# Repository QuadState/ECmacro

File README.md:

# ECmacro

ECmacro is a series of small USB keyboards (macro pads) that use electrostatic capacitive switch parts.
No special external components are needed to read the keys: just the microcontroller's GPIO pins and one resistor per key.

## Models

| | ECmacro 2V | ECmacro 4H |
|---|---|---|
| Features | Volume control; press both keys to mute | Key assignments adjustable in Remap and VIA |
| Microcontroller | CH552E | Seeed Studio XIAO RP2040 |
| Firmware | Custom ([firmware/ch552](firmware/ch552/)) | QMK ([firmware/rp2040](firmware/rp2040/qmk/keyboards/quadstate/ecmacro4h/)) |
| Schematic and PCB | [hardware/2V](hardware/2V/) | [hardware/4H](hardware/4H/) |

## Contents

| Folder | Contents |
|---|---|
| [hardware/](hardware/) | Schematic and PCB for each model (KiCad 10) |
| [firmware/ch552/](firmware/ch552/) | Firmware for the CH552E models; its README covers building and flashing |
| [firmware/rp2040/](firmware/rp2040/) | QMK keyboard definition, VIA definition, build scripts, a udev rule for Linux, and the firmware's [license, source and third-party notices](firmware/rp2040/THIRD-PARTY-NOTICES.txt) |

Case design files are not included.

## USB ID

All models use the USB VID:PID `1209:EC02` ([pid.codes](https://pid.codes/1209/EC02/)).

## License

- Schematics and PCBs (hardware/), images (images/) and documentation outside firmware/rp2040/: CC BY 4.0
- CH552 firmware (firmware/ch552/): MIT
- RP2040 firmware (firmware/rp2040/, including its readme): GPL-2.0-or-later (distributed firmware: GPLv3)

See [LICENSE](LICENSE) for details and [LICENSES/](LICENSES/) for the full texts. For the firmware written on the ECmacro 4H, [firmware/rp2040/THIRD-PARTY-NOTICES.txt](firmware/rp2040/THIRD-PARTY-NOTICES.txt) gives its license, where to get its complete source code, how to build and install it, and its third-party notices.

Copyright (c) 2025–2026 QuadState

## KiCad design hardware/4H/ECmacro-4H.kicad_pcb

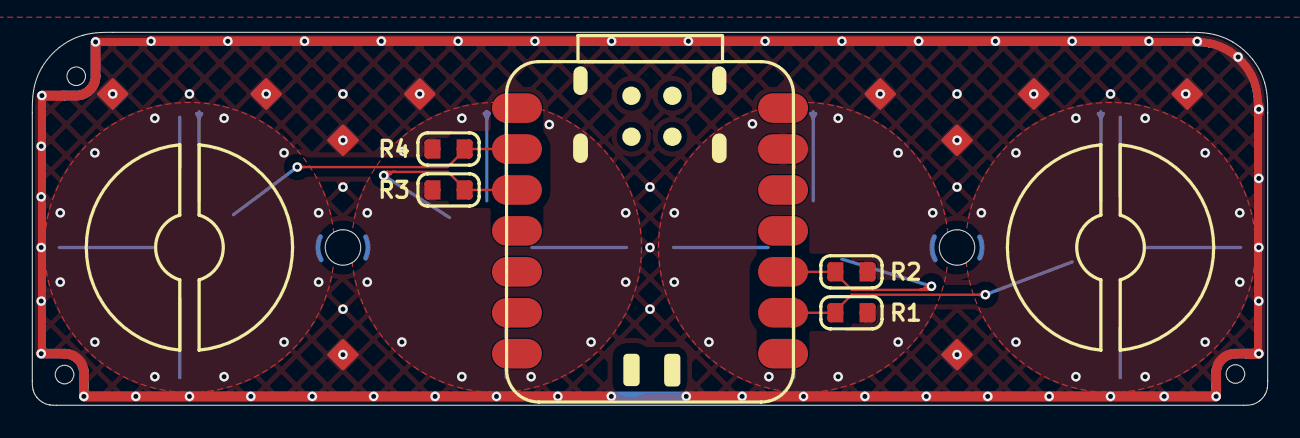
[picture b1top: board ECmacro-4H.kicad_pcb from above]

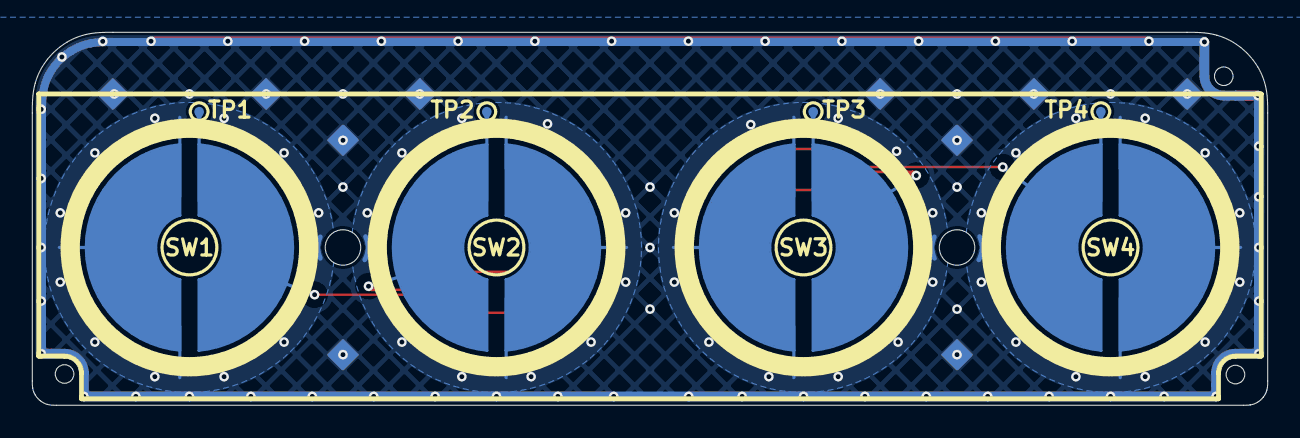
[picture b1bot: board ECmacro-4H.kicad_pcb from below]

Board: 2 copper layers, 76.7 x 23.1 mm, 18 parts (8 on the bottom side), 5 nets.

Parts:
R1, R2, R3, R4: 680kΩ; R_SMD_2012
SW1, SW2, SW3, SW4: SW_Cap; CapacitiveSwitch_16mm
TH1, TH2, TH3: ToolingHole_1.152mm
TH4, TH5: MountingHole_2.2mm_M2
TP1, TP2, TP3, TP4: TestPoint; TestPoint_Pad_D0.6mm
U2: XIAO RP2040; Module_XIAO_RP2040

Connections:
/SW1: R1.1, SW1.2, TP1.1 (1_1), U2.9 (D8)
/SW2: R2.1, SW2.1, TP2.1 (1_1), U2.10 (D9)
/SW3: R3.1, SW3.1, TP3.1 (1_1), U2.3 (D2)
/SW4: R4.1, SW4.1, TP4.1 (1_1), U2.2 (D1)
GND: R1.2, R2.2, R3.2, R4.2, SW1.1, SW2.2, SW3.2, SW4.2, U2.13 (GND)

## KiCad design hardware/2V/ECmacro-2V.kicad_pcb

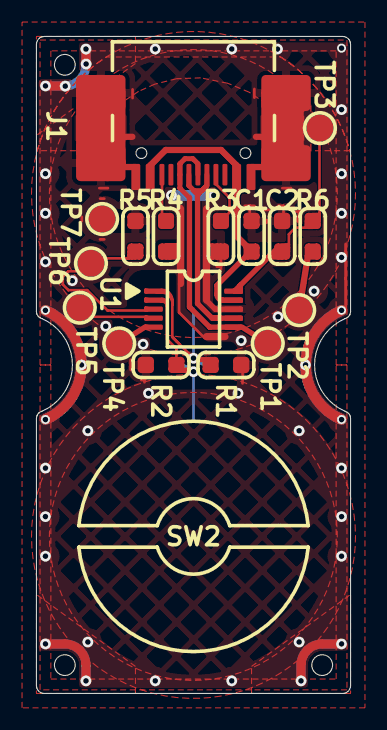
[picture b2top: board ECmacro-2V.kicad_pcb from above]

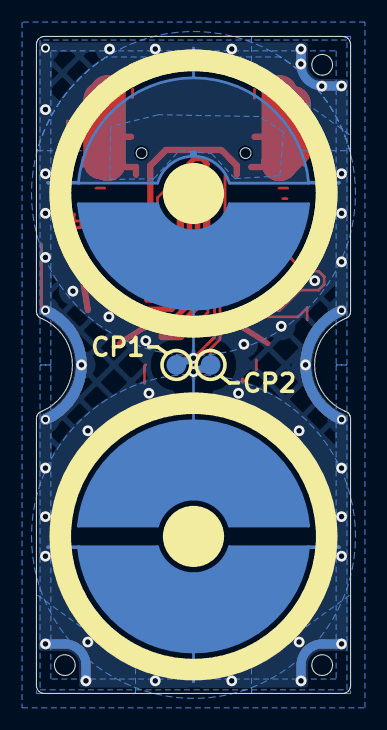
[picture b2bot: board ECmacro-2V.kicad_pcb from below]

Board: 2 copper layers, 17.4 x 36.5 mm, 37 parts (12 on the bottom side), 13 nets.

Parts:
C1, C2: 0.1u; R_0603_1608Metric
CP1, CP2: TestPoint; TestPoint_Pad1.1mm_Mask0.8mm
Dummy1, Dummy2, Dummy3, Dummy5: Keepout_QuarterCircle_R0.5mm
Dummy4: Keepout_QuarterCircle_R1.0mm
Dummy6, Dummy7: Keepout_Circle_D3.0mm
Dummy8, Dummy9, Dummy10: ToolingHole_1.152mm
J1: USB_C_Receptacle_USB2.0_14P; USB_C_Receptacle_USB2.0_SMD
R1, R2: 2MΩ; R_0603_1608Metric
R3, R4: 5.1kΩ; R_0603_1608Metric
R5, R6: 10kΩ; R_0603_1608Metric
SW1: SW_Cap; CapacitiveSwitch_16mm_SplitKeepout
SW2: SW_Cap; CapacitiveSwitch_16mm
SW3, SW6: SW_Cap; CapacitiveSwitch_16mm_Trace_Left
SW4, SW8: SW_Cap; CapacitiveSwitch_16mm_Trace_Center
SW5, SW7: SW_Cap; CapacitiveSwitch_16mm_Trace_Right
TP1, TP2, TP3, TP4, TP5, TP6, TP7: TestPoint; TestPoint_Pad1.5mm_Mask1.2mm
U1: CH552E; IC_MSOP10_3x3mm_P0.5mm

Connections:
/D+: J1.A6 (D+), J1.B6 (D+), TP1.1, U1.6 (P3.6)
/D-: J1.A7 (D-), J1.B7 (D-), U1.7 (P3.7)
/SW1: CP1.1, R1.1, SW1.2, U1.1 (P1.4)
/SW2: CP2.1, R2.1, SW2.1, U1.2 (P1.5)
/TX: TP5.1, U1.4 (P1.7)
/VBUS: C1.1, J1.A4 (VBUS), J1.A9 (VBUS), J1.B4 (VBUS), J1.B9 (VBUS), U1.9 (VDD)
GND: C1.2, C2.2, J1.A1 (GND), J1.A12 (GND), J1.B1 (GND), J1.B12 (GND), J1.S1 (SHIELD), R1.2, R2.2, R3.2, R4.2, R5.1, SW1.1, SW2.2, SW3.1, SW4.1, SW5.1, SW6.1, SW7.1, SW8.1, TP7.1, U1.8 (GND)
unnamed: J1.A5 (CC1), R3.1
unnamed: J1.B5 (CC2), R4.1
unnamed: R6.2, TP2.1
unnamed: R5.2, TP6.1, U1.3 (P1.6)
unnamed: TP4.1, U1.5 (RST)
unnamed: C2.1, R6.1, TP3.1, U1.10 (V33)

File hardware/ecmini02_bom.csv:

Designator,Footprint,Quantity,Value,LCSC Part #
"C1, C2",R_SMD_1608_reflow,2,0.1u,C14663
J1,Connector_USB_C_Receptacle_SMD_reflow4,1,USB_C_Receptacle_USB2.0_14P,C963216
"R1, R2",R_SMD_1608_reflow,2,2MΩ,C22976
"R3, R4",R_SMD_1608_reflow,2,5.1kΩ,C23186
"R5, R6",R_SMD_1608_reflow,2,10kΩ,C25804
U1,IC_SMD_MSOP-10_reflow,1,CH552E,C967938

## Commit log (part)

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2025-04-11 First release
2025-04-13 Rename project from ECmini02 to ECpad02 to avoid name conflict
2025-04-13 Rename project from ECpad02 to ECmicro02 to avoid name conflict
2025-04-28 Renamed project from ECmacro02 to ECmacro.
2025-05-07 Fix: ProductDescriptor
2025-05-13 Add updated KiCad design (ecmacro02_kicad.zip) Update board image Archive old schematic and Gerber files
2025-05-13 Fix README
